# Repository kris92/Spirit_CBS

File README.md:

<p align="center">
  
  </br>
  <font size="6">Pronounce <b>CBS</b> : <b>C</b><i>losed</i> <b>B</b><i>racket</i> <b>S</b><i>lash</i></font>
  </br>
  <font size="4">Work In Progress</font>
</p>

This is an attempt to build a computer somewhere in the middle of an Apple ][ and an Apple //e. So its name is Spirit ]/ (a computer with Apple II series in mind). Since the WAF (Wife Acceptance Factor) of the Apple // form factor (with disk drives and display) is somewhere near zero, I'm looking for something smaller. The first PCB iteration was half size of the System 2 with only a single slot. But one slot is really not enough.<br>
I build a serial USB probe that was really helpful for initial debuging with an interactive step mode. 
<p align="center">
  
  </br>
</p>

So my requirements were :

• Small (For example I choosed Pico ATX and single chips for SRAM(128K) and EEPROM).

• Compatibility with floppy drives (I ❤ how they are sounding).

• Slots. Some hardware Apple II projects exist, but I want floppies and the ability to use some of the cards from my drawers.

• Not necessary 100% compatible.

• Remove on board video to simplify design and HDMI is now possible.

• USB / RF Keyboard

• A2 Joystick

• SSC over USB (FT245) if I have enough space in the CPLD.

3 designs are planned :

• System 1 : 12cm x 12cm board for POC. 4 slots (3 + 1 since slot 0 is a ghost of slot 2 which I used for the keyboard)

• System 2 : 12cm x 14cm board with embeded USB keybpard support. 5 slots.

• System 3 : Apple //c form factor motherboard with //c keyboard support and A2DVI. 3 slots (small form factor. A2heaven like)

For this actual design, I tried to find the right balance between CPLD pins count, the fewest number of external chips and CPLD size for vhdl coding. So the actual result is not perfect but a quite good compromise in my own opinion.

Until now, Disk ][, A2Pico (SD Card), A2DVI and PRODOS-ROM cards were succesfully tested. Since native video generation is not implemented, some games may not working. I will study the possibility to emulate Blanking Softswitches and maybe vapor bits if I can find enough space in the CPLD.

# Status
Full code for System 2 will be released as soon as a stable minimal system will be available.
| System | Date | Status |
| --- | --- | --- |
| <b>System 1</b> | 2025-03-01 | Finished.<br>Floppy, SDCard, USB Keyboard, A2DVI working.<br>Basic test of joystick interface.<br>Prodos 2.4.2 Ok.<br>Some games tested.<br>FastChip splash screen displayed then froze.<br> |
| <b>System 2</b> | 2025-03-31 | Waiting for first PCBs from JLCPCB : Motherboard, SmartPort, Disk ][, //c Keyboard interface.<br>//c keyboard RP2040 code ready. |
| <b>System 3</b> | 2025-03-31 | Initial PCB ordered for case integration test.<br>Riser card PCB ordered for slots. |

# Motherboard

The needed functions of MMU & IOU are coded inside a single CPLD (EPM7128 from Altera).

<p align="center">
  
  </br>
</p>

## PCB
Since size matter here, all resistors, capacitors and leds are SMD. Sorry for through holes fans ;-) But I kept DIL for the main ICs (except FT245).
System 1 & 2 boards density requires a 4 layers design. System will be a classical 2 layers design.

## CPLD vhdl code
I choosed to start from [Apple-II_MiSTer](https://github.com/MiSTer-devel/Apple-II_MiSTer) implementation. Then I made modifications for real hardware interfacing. Finally the vhdl code is quite small.

## USB
The FT245RL is chip was used for initial debugging. When the vhdl code began to be too big, I've build a separate card to do 6502 buses debugging over an USB link. I'm waiting for the next version of the motherboard to check if an I can use the FT245 chip to emulate an onboard Super Serial Card. If SSC can not fit in the CPLD, FT245 may be removed from future designs.

USB Keyboard support is mentionned below.

# Keyboard card

The RP2040 act as the 3660 Pro encoder from the original Apple II. So it generates AKD and KSTRB signals and 7bits ASCII. The pico chip generates the autorepeat features. This is one more thing not to be implemented in the CPLD. The next card release will implement the CTRL-ALT-RESET combination. 2 flavors : USB and //c keyboard.

## build Pico code

```bash
mkdir pico/keyboard/build
cd pico/keyboard/build
cmake ..
git submodule update --init --recursive
make
```

Drag and drop file SpiritKBDBoard.uf2 to the pico

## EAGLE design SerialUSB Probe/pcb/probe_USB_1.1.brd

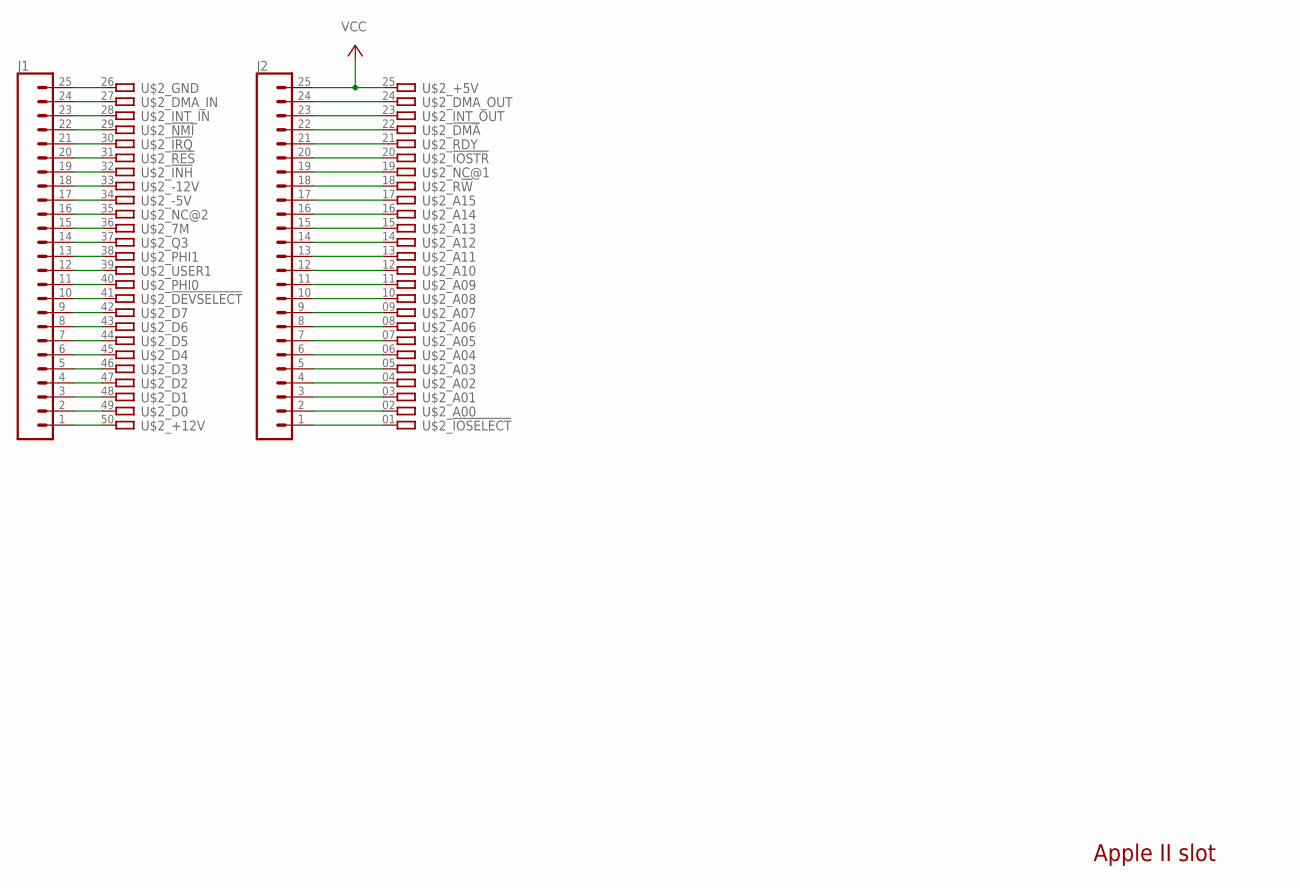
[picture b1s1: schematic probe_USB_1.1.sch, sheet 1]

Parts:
J1, J2: CONN_25PTH_LONGPADS; 1X25_LONGPAD
U$2: A2-50PINSLOT1-3; A2-50PIN-SL1-3

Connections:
!CLKEN: J2.19, U$2.19
!DEV: J1.10, U$2.41; also elsewhere on the board
!I/OSTROBE: J2.20, U$2.20
!IOSEL: J2.1, U$2.01; also elsewhere on the board
!KBD: J1.16, U$2.35
!RES: J1.20, U$2.31; also elsewhere on the board
+5V: J2.25, U$2.25; also elsewhere on the board
A0: J2.2, U$2.02; also elsewhere on the board
A1: J2.3, U$2.03; also elsewhere on the board
A2: J2.4, U$2.04; also elsewhere on the board
A3: J2.5, U$2.05; also elsewhere on the board
A4: J2.6, U$2.06; also elsewhere on the board
A5: J2.7, U$2.07; also elsewhere on the board
A6: J2.8, U$2.08; also elsewhere on the board
A7: J2.9, U$2.09; also elsewhere on the board
A8: J2.10, U$2.10; also elsewhere on the board
A9: J2.11, U$2.11; also elsewhere on the board
A10: J2.12, U$2.12; also elsewhere on the board
A11: J2.13, U$2.13; also elsewhere on the board
A12: J2.14, U$2.14; also elsewhere on the board
A13: J2.15, U$2.15; also elsewhere on the board
A14: J2.16, U$2.16; also elsewhere on the board
A15: J2.17, U$2.17; also elsewhere on the board
D0: J1.2, U$2.49; also elsewhere on the board
D1: J1.3, U$2.48; also elsewhere on the board
D2: J1.4, U$2.47; also elsewhere on the board
D3: J1.5, U$2.46; also elsewhere on the board
D4: J1.6, U$2.45; also elsewhere on the board
D5: J1.7, U$2.44; also elsewhere on the board
D6: J1.8, U$2.43; also elsewhere on the board
D7: J1.9, U$2.42; also elsewhere on the board
DMA_IN: J1.24, U$2.27
GND: J1.25, U$2.26; also elsewhere on the board
INT_IN: J1.23, U$2.28
unnamed: J1.22, U$2.29
unnamed: J2.22, U$2.22
unnamed: J2.23, U$2.23
unnamed: J2.24, U$2.24
unnamed: J1.21, U$2.30
unnamed: J1.19, U$2.32
unnamed: J1.18, U$2.33
unnamed: J1.17, U$2.34
unnamed: J1.15, U$2.36
unnamed: J1.14, U$2.37
unnamed: J1.1, U$2.50
PHI0: J1.11, U$2.40; also elsewhere on the board
PHI1: J1.13, U$2.38; also elsewhere on the board
R/!W: J2.18, U$2.18; also elsewhere on the board
RDY: J2.21, U$2.21; also elsewhere on the board
SYNC: J1.12, U$2.39; also elsewhere on the board

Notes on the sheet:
Apple II slot

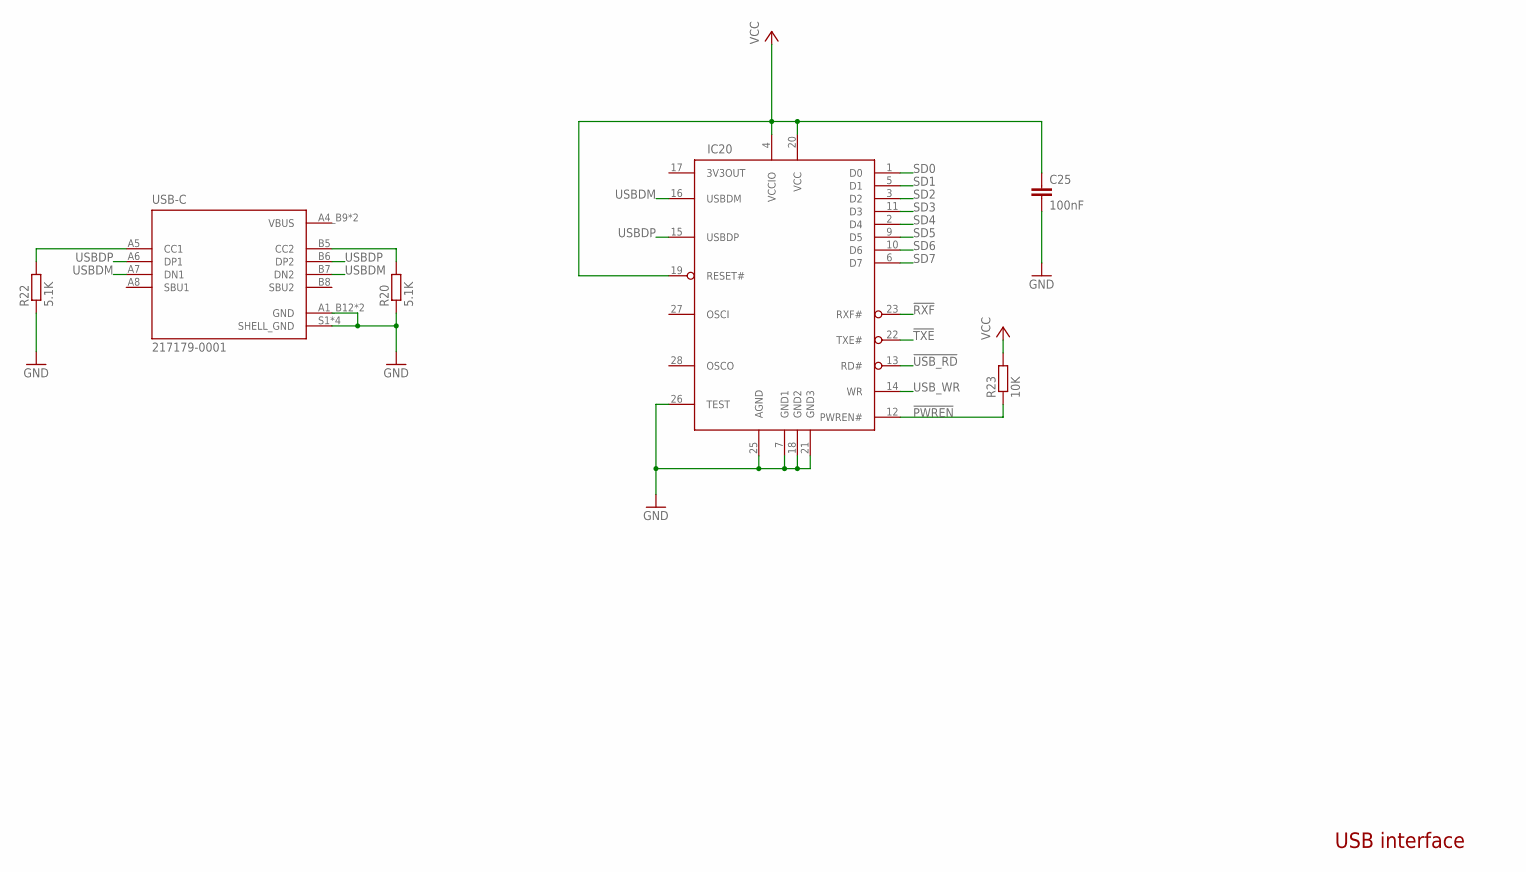
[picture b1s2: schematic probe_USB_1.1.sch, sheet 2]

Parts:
C25: 100nF; C0805
IC20: FT245RL; SSOP28DB
R20, R22: 5.1K; R0805
R23: 10K; R0805
USB-C: 217179-0001; GCT_USB4105-GF-A

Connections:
!PWREN: IC20.12 (PWREN#), R23.1
!RXF: IC20.23 (RXF#); also elsewhere on the board
!TXE: IC20.22 (TXE#); also elsewhere on the board
!USB_RD: IC20.13 (RD#); also elsewhere on the board
+5V: C25.1, IC20.4 (VCCIO), IC20.19 (RESET#), IC20.20 (VCC), R23.2; also elsewhere on the board
GND: C25.2, IC20.7 (GND1), IC20.18 (GND2), IC20.21 (GND3), IC20.25 (AGND), IC20.26 (TEST), R20.1, R22.1, USB-C.A1_B12 (GND), USB-C.B1_A12 (GND), USB-C.S1 (SHELL_GND), USB-C.S2 (SHELL_GND), USB-C.S3 (SHELL_GND), USB-C.S4 (SHELL_GND); also elsewhere on the board
unnamed: R22.2, USB-C.A5 (CC1)
unnamed: R20.2, USB-C.B5 (CC2)
SD0: IC20.1 (D0); also elsewhere on the board
SD1: IC20.5 (D1); also elsewhere on the board
SD2: IC20.3 (D2); also elsewhere on the board
SD3: IC20.11 (D3); also elsewhere on the board
SD4: IC20.2 (D4); also elsewhere on the board
SD5: IC20.9 (D5); also elsewhere on the board
SD6: IC20.10 (D6); also elsewhere on the board
SD7: IC20.6 (D7); also elsewhere on the board
USBDM: IC20.16 (USBDM), USB-C.A7 (DN1), USB-C.B7 (DN2)
USBDP: IC20.15 (USBDP), USB-C.A6 (DP1), USB-C.B6 (DP2)
USB_WR: IC20.14 (WR); also elsewhere on the board
VBUS: USB-C.A4_B9 (VBUS), USB-C.B4_A9 (VBUS)

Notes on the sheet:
USB interface

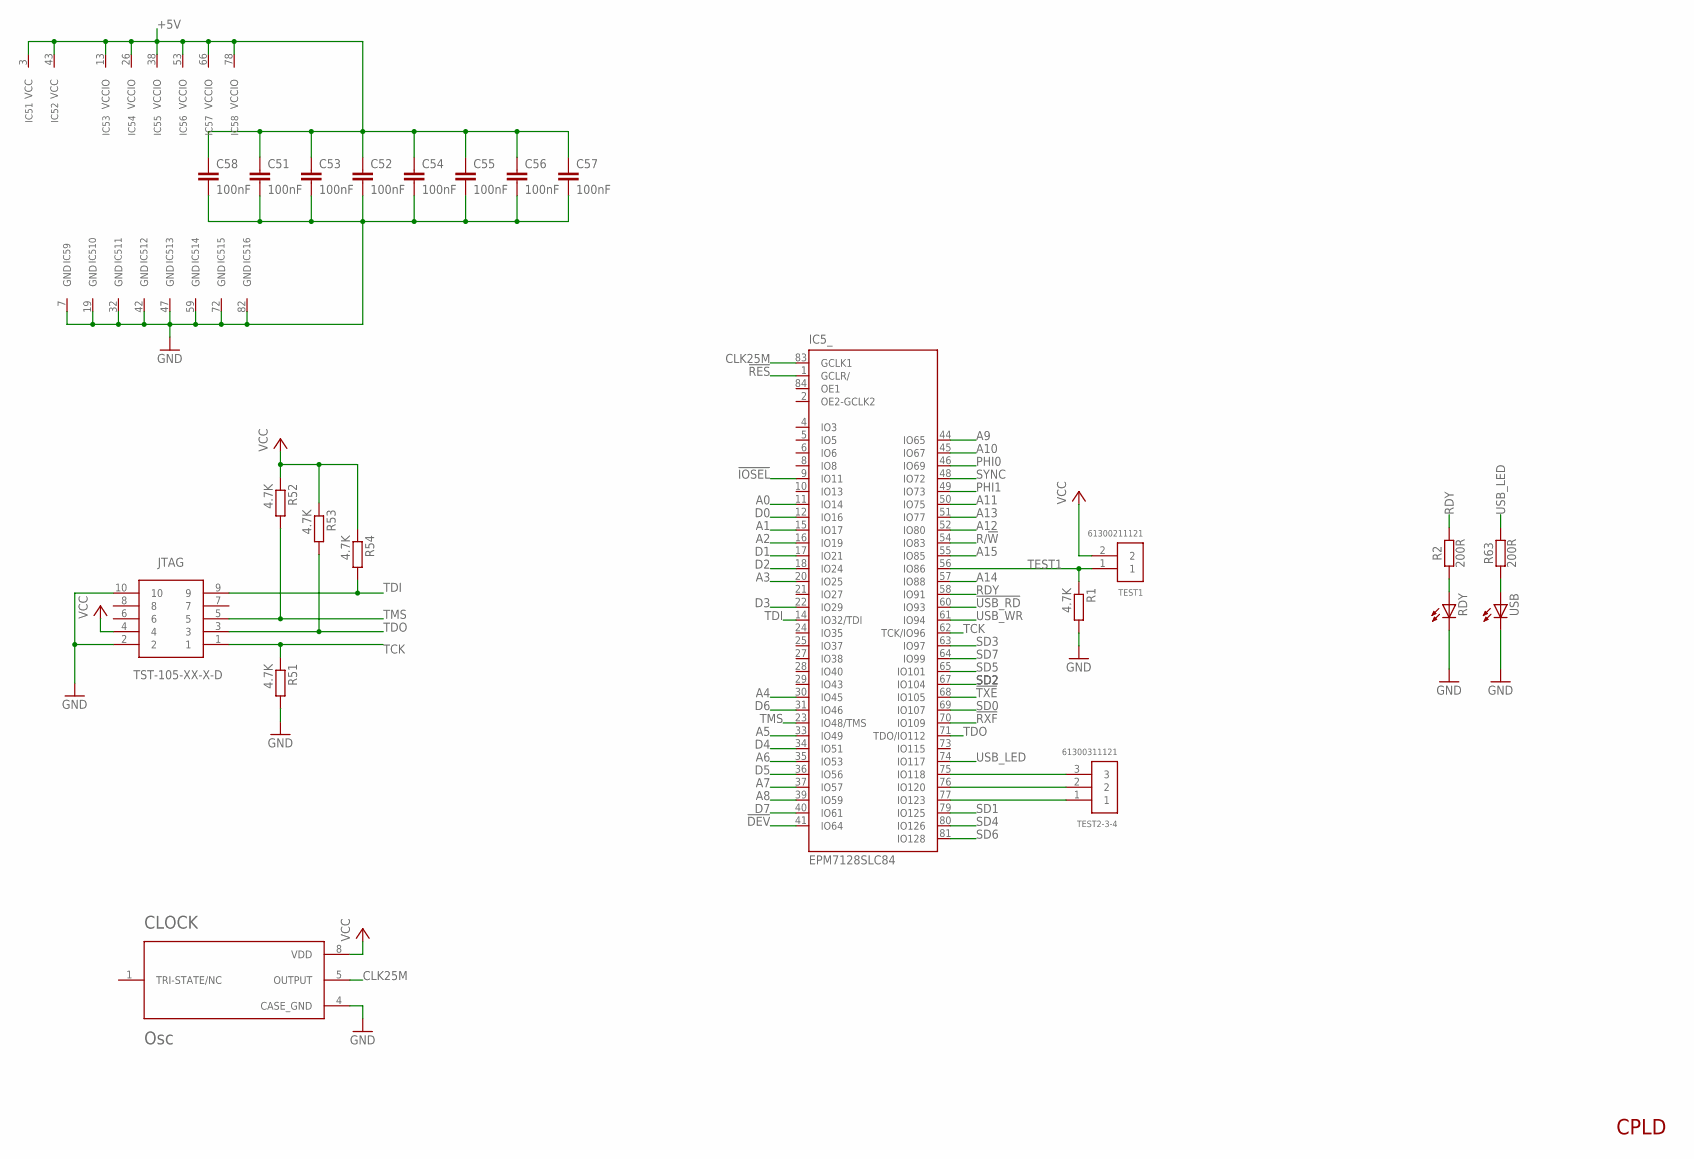
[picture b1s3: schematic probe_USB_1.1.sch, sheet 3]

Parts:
C51, C52, C53, C54, C55, C56, C57, C58: 100nF; C0805
CLOCK: Osc; OSC762W46P254L1270H639Q8
IC5: EPM7128SLC84; 9404408424000000
JTAG: TST-105-XX-X-D
R1, R51, R52, R53, R54: 4.7K; R0805
R2, R63: 200R; R0805
RDY: APTD2012LSURCK; CHIP-LED0805
TEST1: 61300211121
TEST2-3-4: 61300311121
USB: APTD2012LCGCK; CHIP-LED0805

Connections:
!DEV: IC5.41 (IO64); also elsewhere on the board
!IOSEL: IC5.9 (IO11); also elsewhere on the board
!RES: IC5.1 (GCLR/); also elsewhere on the board
!RXF: IC5.70 (IO109); also elsewhere on the board
!TXE: IC5.68 (IO105); also elsewhere on the board
!USB_RD: IC5.60 (IO93); also elsewhere on the board
+5V: C51.1, C52.1, C53.1, C54.1, C55.1, C56.1, C57.1, C58.1, CLOCK.8 (VDD), IC5.3 (VCC), IC5.13 (VCCIO), IC5.26 (VCCIO), IC5.38 (VCCIO), IC5.43 (VCC), IC5.53 (VCCIO), IC5.66 (VCCIO), IC5.78 (VCCIO), JTAG.4, R52.1, R53.1, R54.1, TEST1.2; also elsewhere on the board
A0: IC5.11 (IO14); also elsewhere on the board
A1: IC5.15 (IO17); also elsewhere on the board
A2: IC5.16 (IO19); also elsewhere on the board
A3: IC5.20 (IO25); also elsewhere on the board
A4: IC5.30 (IO45); also elsewhere on the board
A5: IC5.33 (IO49); also elsewhere on the board
A6: IC5.35 (IO53); also elsewhere on the board
A7: IC5.37 (IO57); also elsewhere on the board
A8: IC5.39 (IO59); also elsewhere on the board
A9: IC5.44 (IO65); also elsewhere on the board
A10: IC5.45 (IO67); also elsewhere on the board
A11: IC5.50 (IO75); also elsewhere on the board
A12: IC5.52 (IO80); also elsewhere on the board
A13: IC5.51 (IO77); also elsewhere on the board
A14: IC5.57 (IO88); also elsewhere on the board
A15: IC5.55 (IO85); also elsewhere on the board
CLK25M: CLOCK.5 (OUTPUT), IC5.83 (GCLK1)
D0: IC5.12 (IO16); also elsewhere on the board
D1: IC5.17 (IO21); also elsewhere on the board
D2: IC5.18 (IO24); also elsewhere on the board
D3: IC5.22 (IO29); also elsewhere on the board
D4: IC5.34 (IO51); also elsewhere on the board
D5: IC5.36 (IO56); also elsewhere on the board
D6: IC5.31 (IO46); also elsewhere on the board
D7: IC5.40 (IO61); also elsewhere on the board
GND: C51.2, C52.2, C53.2, C54.2, C55.2, C56.2, C57.2, C58.2, CLOCK.4 (CASE_GND), IC5.7 (GND), IC5.19 (GND), IC5.32 (GND), IC5.42 (GND), IC5.47 (GND), IC5.59 (GND), IC5.72 (GND), IC5.82 (GND), JTAG.2, JTAG.10, R1.2, R51.2, RDY.C, USB.C; also elsewhere on the board
unnamed: IC5.75 (IO118), TEST2-3-4.3
unnamed: R2.1, RDY.A
unnamed: IC5.76 (IO120), TEST2-3-4.2
unnamed: IC5.77 (IO123), TEST2-3-4.1
unnamed: R63.1, USB.A
PHI0: IC5.46 (IO69); also elsewhere on the board
PHI1: IC5.49 (IO73); also elsewhere on the board
R/!W: IC5.54 (IO83); also elsewhere on the board
RDY: IC5.58 (IO91), R2.2; also elsewhere on the board
SD0: IC5.69 (IO107); also elsewhere on the board
SD1: IC5.79 (IO125); also elsewhere on the board
SD2: IC5.67 (IO104); also elsewhere on the board
SD3: IC5.63 (IO97); also elsewhere on the board
SD4: IC5.80 (IO126); also elsewhere on the board
SD5: IC5.65 (IO101); also elsewhere on the board
SD6: IC5.81 (IO128); also elsewhere on the board
SD7: IC5.64 (IO99); also elsewhere on the board
SYNC: IC5.48 (IO72); also elsewhere on the board
TCK: IC5.62 (TCK/IO96), JTAG.1, R51.1
TDI: IC5.14 (IO32/TDI), JTAG.9, R54.2
TDO: IC5.71 (TDO/IO112), JTAG.3, R53.2
TEST1: IC5.56 (IO86), R1.1, TEST1.1
TMS: IC5.23 (IO48/TMS), JTAG.5, R52.2
USB_LED: IC5.74 (IO117), R63.2
USB_WR: IC5.61 (IO94); also elsewhere on the board

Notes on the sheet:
CPLD

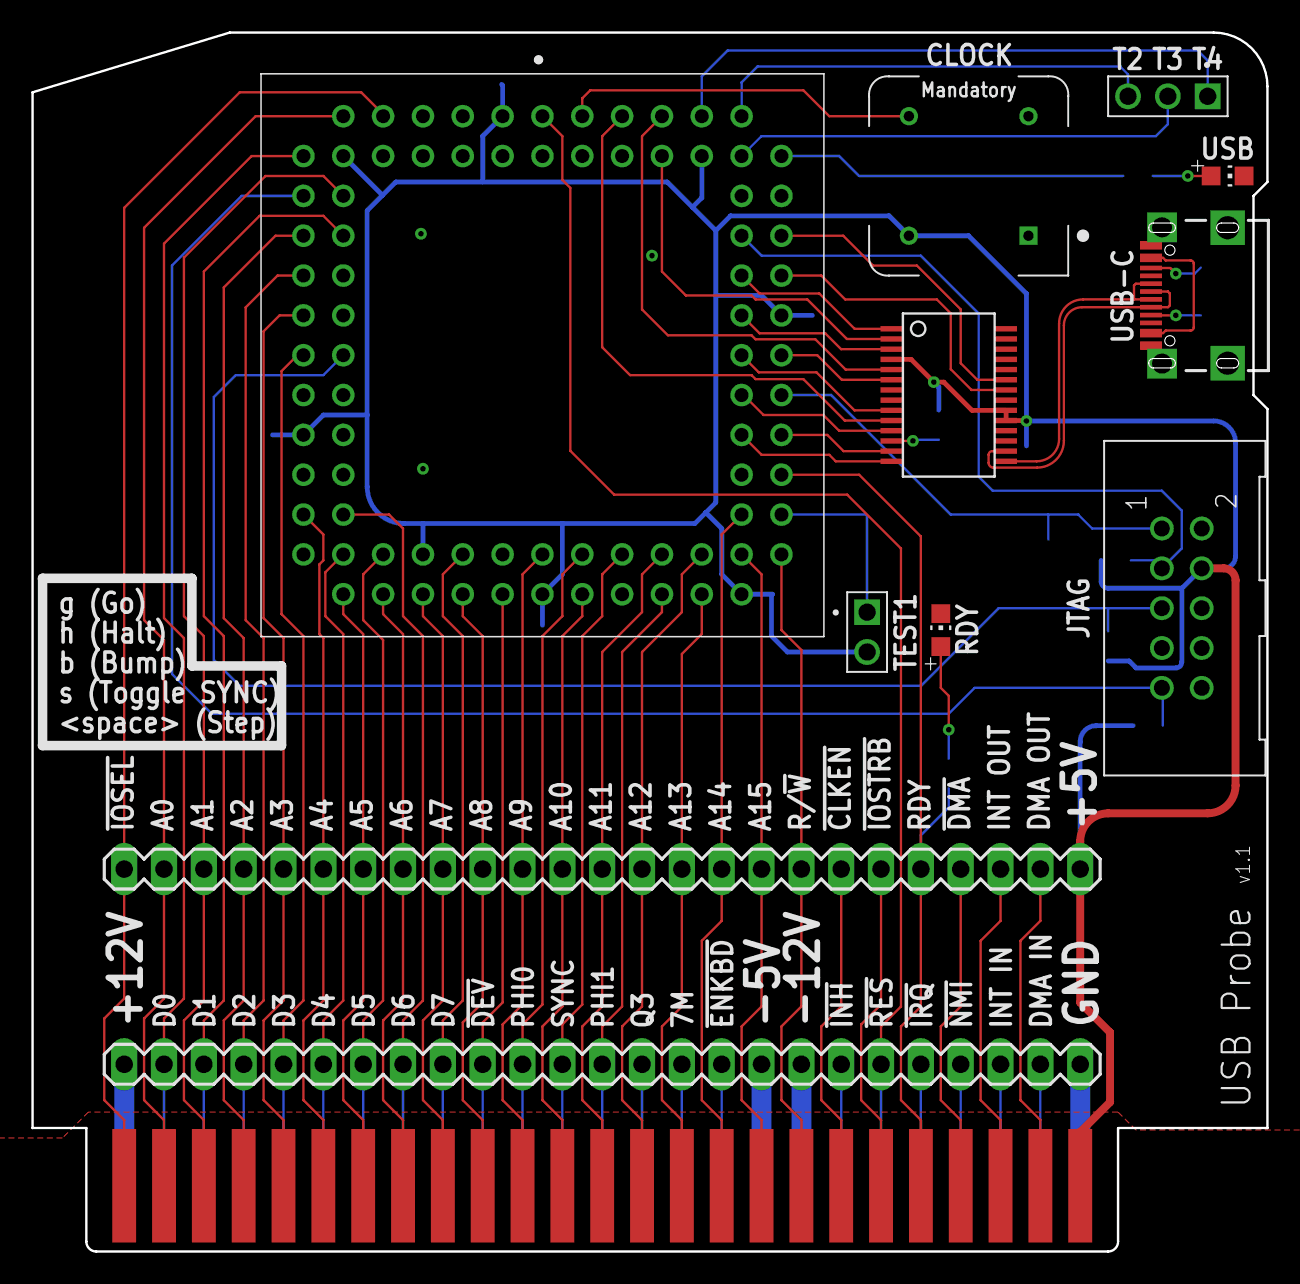
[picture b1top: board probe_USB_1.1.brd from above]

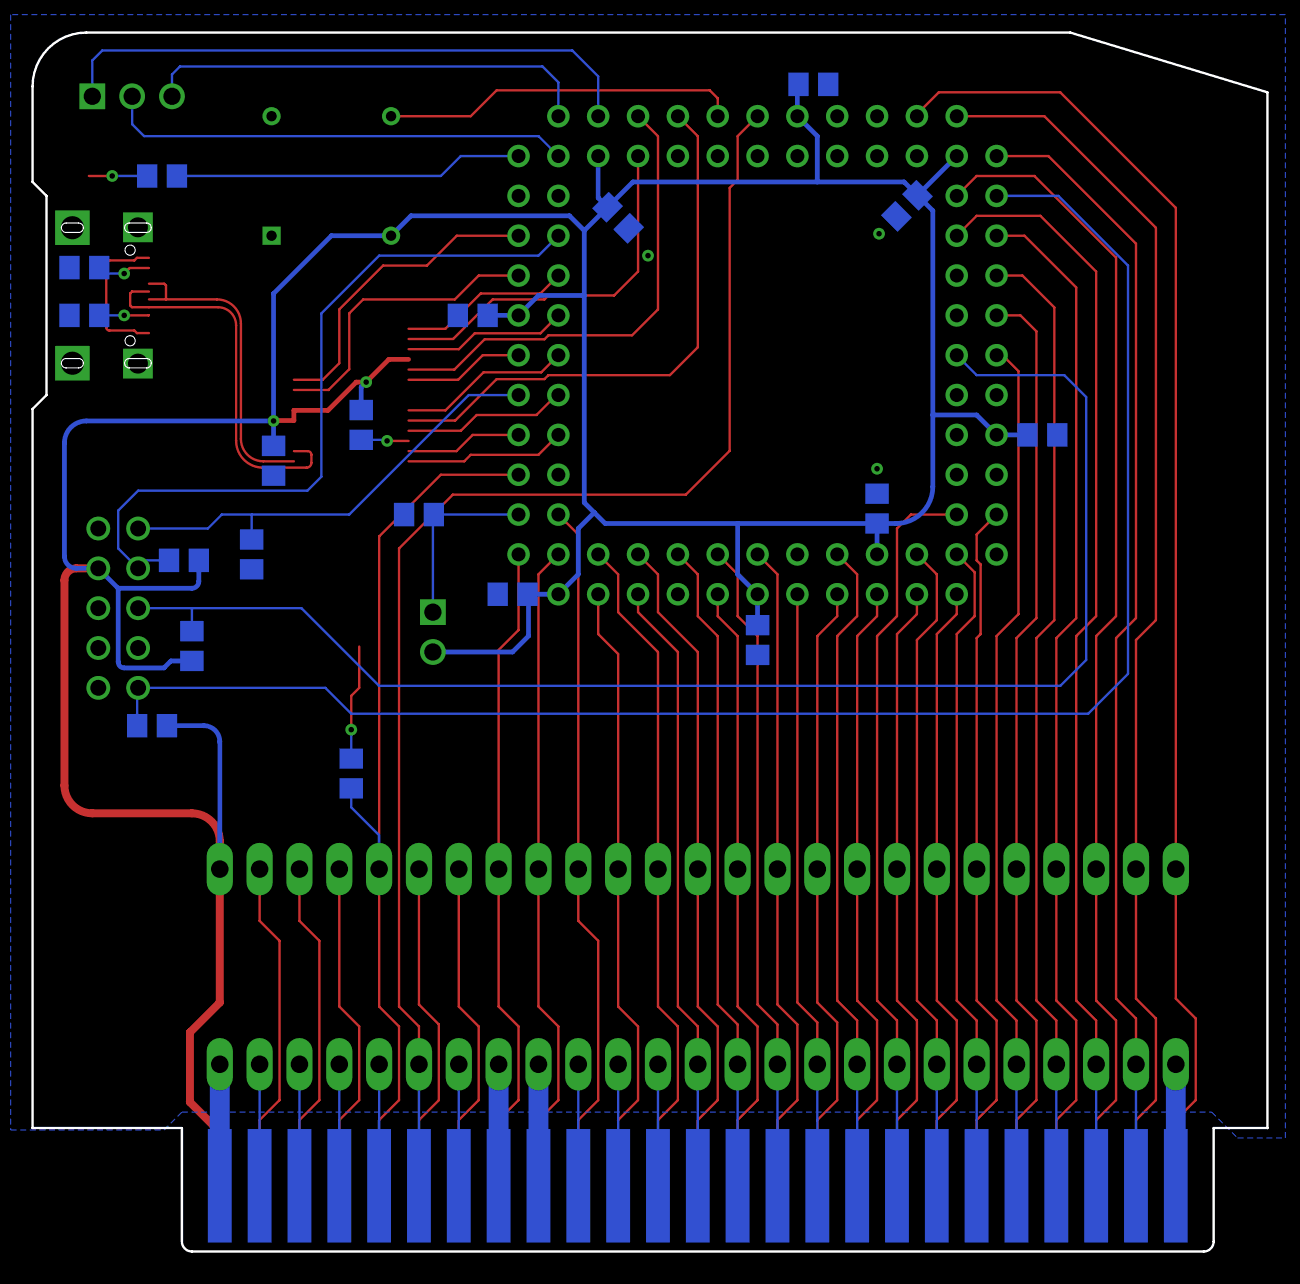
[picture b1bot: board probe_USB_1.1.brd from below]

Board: 2 copper layers, 78.7 x 77.7 mm, 31 parts (19 on the bottom side), 80 nets.

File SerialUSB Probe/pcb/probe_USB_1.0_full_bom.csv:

Comment,Designator,Footprint,LCSC Part #
217179-0001,USB-C,GCT_USB4105-GF-A,C3197684
APTD2012LCGCK,USB,CHIP-LED0805,C5366381
APTD2012LSURCK,RDY,CHIP-LED0805,C5366382
FT245RL,IC20,SSOP28DB,C12633
4.7K,R1 R51 R52 R53 R54,R0805,C17673
5.1K,R20 R22,R0805,C27834
10K,R23,R0805,C17414
100nF,C25 C51 C52 C53 C54 C55 C56 C57 C58,C0805,C49678
200R,R2 R63,R0805,C17540

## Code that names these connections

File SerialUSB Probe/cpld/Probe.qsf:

# -------------------------------------------------------------------------- #
#
# Copyright (C) 1991-2013 Altera Corporation
# Your use of Altera Corporation's design tools, logic functions 
# and other software and tools, and its AMPP partner logic 
# functions, and any output files from any of the foregoing 
# (including device programming or simulation files), and any 
# associated documentation or information are expressly subject 
# to the terms and conditions of the Altera Program License 
# Subscription Agreement, Altera MegaCore Function License 
# Agreement, or other applicable license agreement, including, 
# without limitation, that your use is for the sole purpose of 
# programming logic devices manufactured by Altera and sold by 
# Altera or its authorized distributors.  Please refer to the 
# applicable agreement for further details.
#
# -------------------------------------------------------------------------- #
#
# Quartus II 64-Bit
# Version 13.0.1 Build 232 06/12/2013 Service Pack 1 SJ Web Edition
# Date created = 22:29:05  February 16, 2025
#
# -------------------------------------------------------------------------- #
#
# Notes:
#
# 1) The default values for assignments are stored in the file:
#		Echo_assignment_defaults.qdf
#    If this file doesn't exist, see file:
#		assignment_defaults.qdf
#
# 2) Altera recommends that you do not modify this file. This
#    file is updated automatically by the Quartus II software
#    and any changes you make may be lost or overwritten.
#
# -------------------------------------------------------------------------- #


set_global_assignment -name FAMILY MAX7000S
set_global_assignment -name DEVICE "EPM7128SLC84-10"
set_global_assignment -name TOP_LEVEL_ENTITY Probe
set_global_assignment -name ORIGINAL_QUARTUS_VERSION "13.0 SP1"
set_global_assignment -name PROJECT_CREATION_TIME_DATE "22:29:05  FEBRUARY 16, 2025"
set_global_assignment -name LAST_QUARTUS_VERSION "13.0 SP1"
set_global_assignment -name PROJECT_OUTPUT_DIRECTORY output_files
set_global_assignment -name ERROR_CHECK_FREQUENCY_DIVISOR "-1"
set_global_assignment -name MIN_CORE_JUNCTION_TEMP 0
set_global_assignment -name MAX_CORE_JUNCTION_TEMP 85
set_global_assignment -name NUM_PARALLEL_PROCESSORS 1
set_global_assignment -name ALLOW_POWER_UP_DONT_CARE OFF
set_global_assignment -name RESERVE_ALL_UNUSED_PINS_NO_OUTPUT_GND "AS INPUT TRI-STATED"

#set_location_assignment PIN_83 -to CLK12M
set_location_assignment PIN_46 -to PHI_0

#set_location_assignment PIN_56 -to TEST1
#set_location_assignment PIN_75 -to TEST2
#set_location_assignment PIN_76 -to TEST3
#set_location_assignment PIN_77 -to TEST4

# Interrupts
set_location_assignment PIN_1 -to nRESET

# CPU
set_location_assignment PIN_54 -to RnW
set_location_assignment PIN_58 -to RDY
set_location_assignment PIN_48 -to SYNC

# Slot
#set_location_assignment PIN_9 -to nIOSEL
#set_location_assignment PIN_41 -to nDEV
#set_location_assignment PIN_9 -to nIO_STROBE

# CPU addresses bus
set_location_assignment PIN_11 -to A[0]
set_location_assignment PIN_15 -to A[1]
set_location_assignment PIN_16 -to A[2]
set_location_assignment PIN_20 -to A[3]
set_location_assignment PIN_30 -to A[4]
set_location_assignment PIN_33 -to A[5]
set_location_assignment PIN_35 -to A[6]
set_location_assignment PIN_37 -to A[7]
set_location_assignment PIN_39 -to A[8]
set_location_assignment PIN_44 -to A[9]
set_location_assignment PIN_45 -to A[10]
set_location_assignment PIN_50 -to A[11]
set_location_assignment PIN_52 -to A[12]
set_location_assignment PIN_51 -to A[13]
set_location_assignment PIN_57 -to A[14]
set_location_assignment PIN_55 -to A[15]

# Data bus
set_location_assignment PIN_12 -to D[0]
set_location_assignment PIN_17 -to D[1]
set_location_assignment PIN_18 -to D[2]
set_location_assignment PIN_22 -to D[3]
set_location_assignment PIN_34 -to D[4]
set_location_assignment PIN_36 -to D[5]
set_location_assignment PIN_31 -to D[6]
set_location_assignment PIN_40 -to D[7]

# FT245
set_location_assignment PIN_60 -to nUSB_RD
set_location_assignment PIN_61 -to USB_WR
set_location_assignment PIN_70 -to nRXF
set_location_assignment PIN_68 -to nTXE
set_location_assignment PIN_69 -to SD[0]
set_location_assignment PIN_79 -to SD[1]
set_location_assignment PIN_67 -to SD[2]
set_location_assignment PIN_63 -to SD[3]
set_location_assignment PIN_80 -to SD[4]
set_location_assignment PIN_65 -to SD[5]
set_location_assignment PIN_81 -to SD[6]
set_location_assignment PIN_64 -to SD[7]
set_location_assignment PIN_74 -to USB_LED

set_global_assignment -name SDC_FILE Probe.sdc
set_global_assignment -name VHDL_FILE Probe.vhdl
set_global_assignment -name VHDL_FILE DebugConsole.vhdl
set_global_assignment -name MAX7000_OPTIMIZATION_TECHNIQUE AREA
set_global_assignment -name MAX7000_DEVICE_IO_STANDARD "3.3-V LVTTL"
set_global_assignment -name USE_CONFIGURATION_DEVICE ON

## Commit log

2025-04-02 Prepare System 2 repo
2025-04-02 Probe image
2025-04-02 Serial USB Probe

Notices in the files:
parts and their libraries:
SparkFun-Connectors: Licensing: Creative Commons ShareAlike 4.0 International - https://creativecommons.org/licenses/by-sa/4.0
